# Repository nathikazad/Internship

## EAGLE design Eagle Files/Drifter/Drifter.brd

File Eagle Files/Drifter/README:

The PCB that got printed doest not have vcc connected on the RS485 chip, I updated that error on the eagle files afterwards

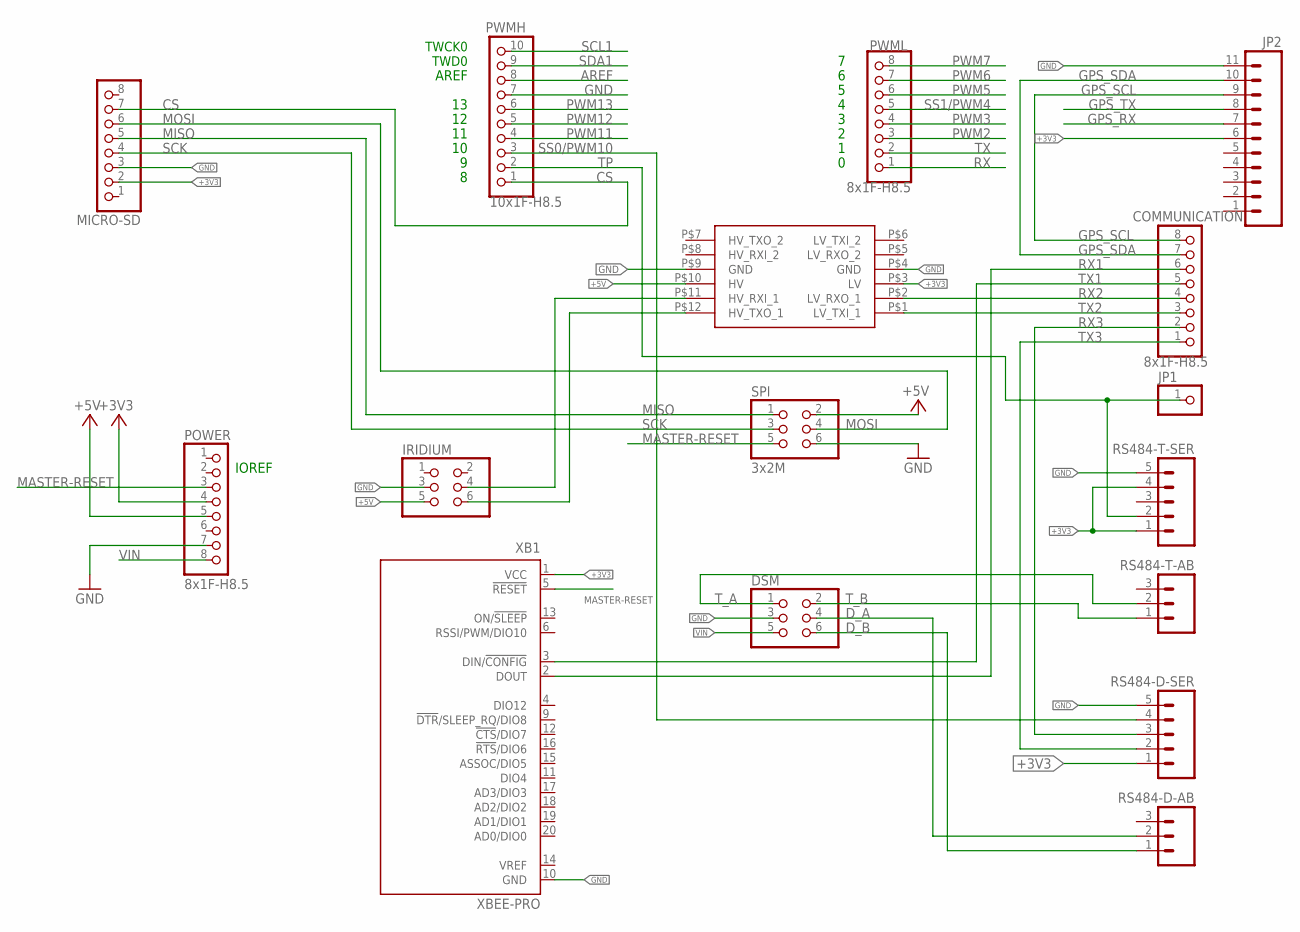
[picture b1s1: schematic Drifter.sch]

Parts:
COMMUNICATION: 8x1F-H8.5; 1X08
DSM: PINHD-2X3; 2X03
IRIDIUM: PINHD-2X3; 2X03
JP1: PINHD-1X1; 1X01
JP2: M111.27MM; 1X11-1.27MM
MICRO-SD: PINHD-1X8BIG; 1X08-BIG
POWER: 8x1F-H8.5; 1X08
PWMH: 10x1F-H8.5; 1X10
PWML: 8x1F-H8.5; 1X08
RS484-D-AB, RS484-T-AB: M03PTH; 1X03
RS484-D-SER, RS484-T-SER: M05PTH; 1X05
SPI: 3x2M; 2X03
U$1: LOGIC_LEVEL_CONVERTER
XB1: XBEE-PRO

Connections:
+3V3: JP2.6, MICRO-SD.2, POWER.4, RS484-D-SER.1, RS484-T-SER.1, RS484-T-SER.4, U$1.P$3 (LV), XB1.1 (VCC)
+5V: IRIDIUM.5, POWER.5, SPI.2, U$1.P$10 (HV)
AREF: PWMH.8
CS: MICRO-SD.7, PWMH.1
D_A: DSM.4, RS484-D-AB.2
D_B: DSM.6, RS484-D-AB.1
GND: DSM.3, IRIDIUM.3, JP2.11, MICRO-SD.3, POWER.7, PWMH.7, RS484-D-SER.5, RS484-T-SER.5, SPI.6, U$1.P$4 (GND), U$1.P$9 (GND), XB1.10 (GND)
GPS_RX: JP2.7
GPS_SCL: COMMUNICATION.8, JP2.9
GPS_SDA: COMMUNICATION.7, JP2.10
GPS_TX: JP2.8
MASTER-RESET: POWER.3, SPI.5, XB1.5 (!RESET)
MISO: MICRO-SD.5, SPI.1
MOSI: MICRO-SD.6, SPI.4
unnamed: IRIDIUM.4, U$1.P$11 (HV_RXI_1)
unnamed: IRIDIUM.6, U$1.P$12 (HV_TXO_1)
PWM2: PWML.3
PWM3: PWML.4
PWM5: PWML.6
PWM6: PWML.7
PWM7: PWML.8
PWM11: PWMH.4
PWM12: PWMH.5
PWM13: PWMH.6
RX: PWML.1
RX1: COMMUNICATION.6, XB1.2 (DOUT)
RX2: COMMUNICATION.4, U$1.P$2 (LV_RXO_1)
RX3: COMMUNICATION.2, RS484-D-SER.3
SCK: MICRO-SD.4, SPI.3
SCL1: PWMH.10
SDA1: PWMH.9
SS0/PWM10: PWMH.3, RS484-D-SER.4
SS1/PWM4: PWML.5
TP: JP1.1, PWMH.2, RS484-T-SER.2
TX: PWML.2
TX1: COMMUNICATION.5, XB1.3 (DIN/!CONFIG)
TX2: COMMUNICATION.3, U$1.P$1 (LV_TXI_1)
TX3: COMMUNICATION.1, RS484-D-SER.2
T_A: DSM.1, RS484-T-AB.2
T_B: DSM.2, RS484-T-AB.1
VIN: DSM.5, POWER.8

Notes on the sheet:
IOREF
TWCK0
TWD0
AREF

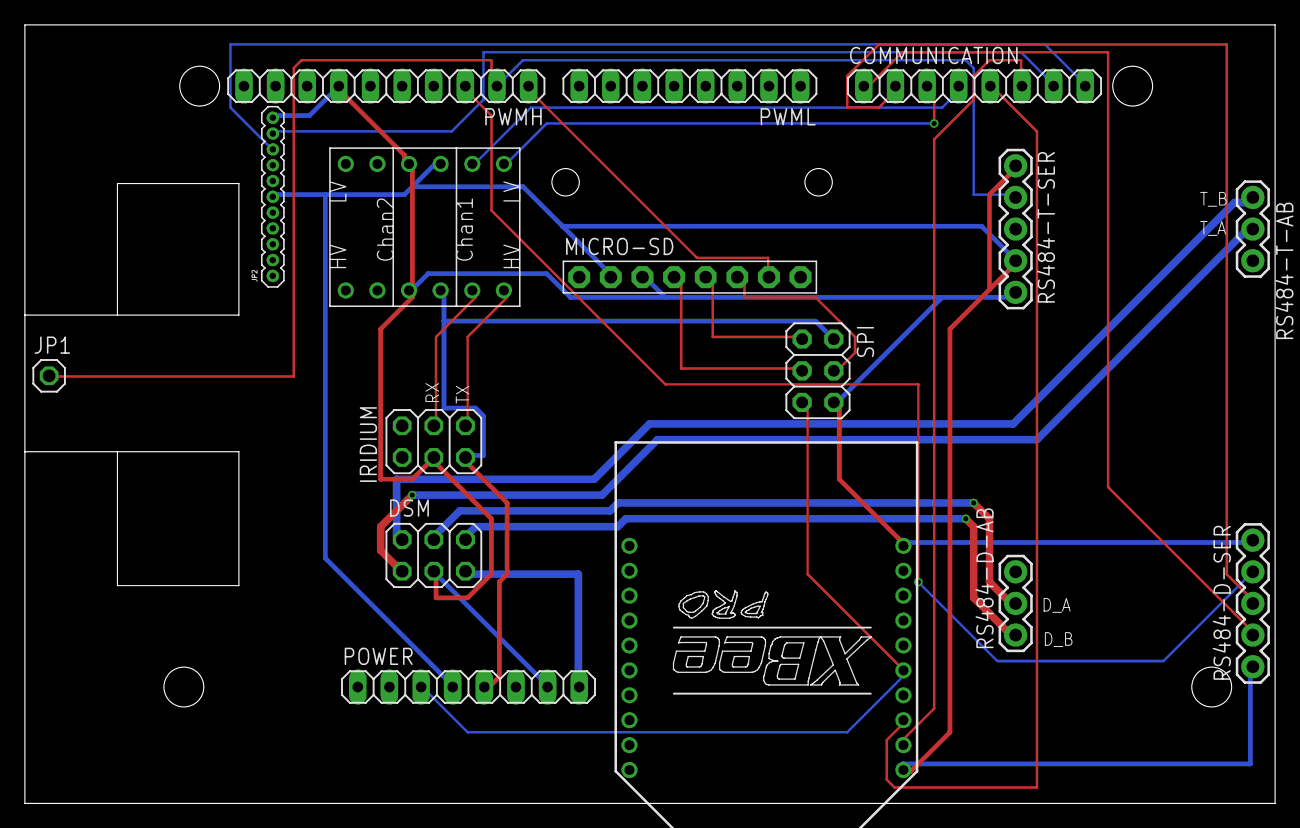
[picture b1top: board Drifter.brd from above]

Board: 2 copper layers, 100.4 x 62.5 mm, 16 parts (0 on the bottom side), 25 nets.

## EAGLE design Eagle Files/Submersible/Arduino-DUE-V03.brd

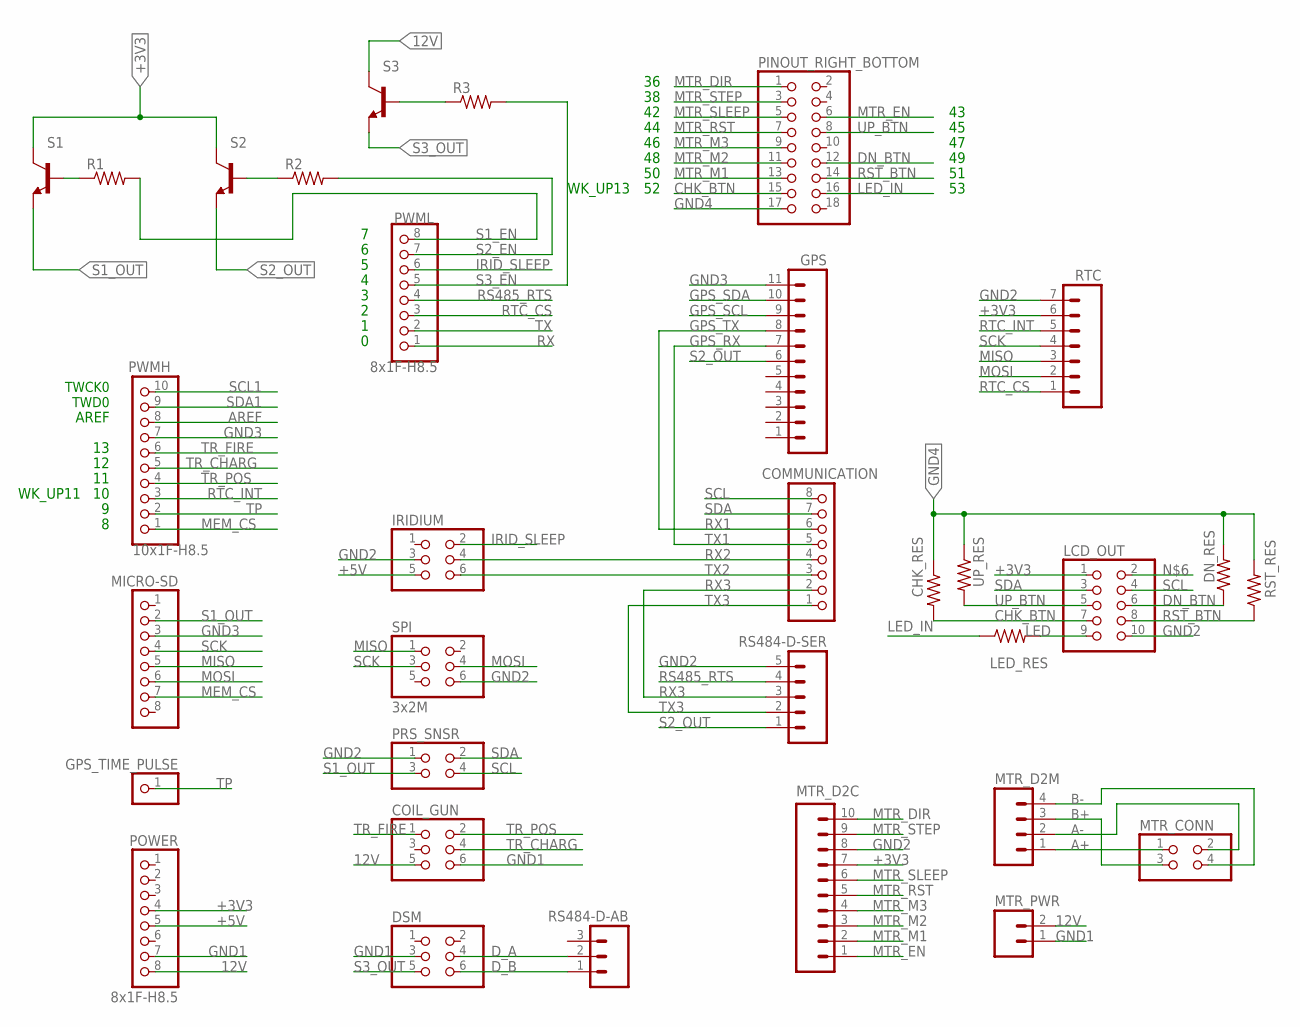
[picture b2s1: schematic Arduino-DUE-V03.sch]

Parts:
CHK_RES: RESISTORPTH-1/4W; AXIAL-0.4
COIL_GUN: PINHD-2X3; 2X03
COMMUNICATION: 8x1F-H8.5; 1X08
DN_RES: RESISTORPTH-1/4W; AXIAL-0.4
DSM: PINHD-2X3; 2X03
GPS: M111.27MM; 1X11-1.27MM
GPS_TIME_PULSE: PINHD-1X1; 1X01
IRIDIUM: PINHD-2X3; 2X03
LCD_OUT: PINHD-2X5; 2X05
LED_RES: RESISTORPTH-1/4W; AXIAL-0.4
MICRO-SD: PINHD-1X8BIG; 1X08-BIG
MTR_CONN: PINHD-2X2; 2X02
MTR_D2C: M10SILK_FEMALE_PTH; 1X10
MTR_D2M: M04NO_SILK_ALL_ROUND; 1X04_NO_SILK_ALL_ROUND
MTR_PWR: M02PTH; 1X02
PINOUT_RIGHT_BOTTOM: PINHD-2X9; 2X09
POWER: 8x1F-H8.5; 1X08
PRS_SNSR: PINHD-2X2; 2X02
PWMH: 10x1F-H8.5; 1X10
PWML: 8x1F-H8.5; 1X08
R1, R2, R3: RESISTORPTH-1/4W; AXIAL-0.4
RS484-D-AB: M03PTH; 1X03
RS484-D-SER: M05PTH; 1X05
RST_RES: RESISTORPTH-1/4W; AXIAL-0.4
RTC: M07; 1X07
S1, S2, S3: 2N3904; TO92
SPI: 3x2M; 2X03
UP_RES: RESISTORPTH-1/4W; AXIAL-0.4

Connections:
12V: COIL_GUN.5, MTR_PWR.2, POWER.8, S3.1 (C)
+3V3: LCD_OUT.1, MTR_D2C.7, POWER.4, RTC.6, S1.1 (C), S2.1 (C)
+5V: IRIDIUM.5, POWER.5
A+: MTR_CONN.1, MTR_D2M.1
A-: MTR_CONN.2, MTR_D2M.2
AREF: PWMH.8
B+: MTR_CONN.3, MTR_D2M.3
B-: MTR_CONN.4, MTR_D2M.4
CHK_BTN: CHK_RES.P$2 (2), LCD_OUT.7, PINOUT_RIGHT_BOTTOM.15
DN_BTN: DN_RES.P$1 (1), LCD_OUT.6, PINOUT_RIGHT_BOTTOM.12
D_A: DSM.4, RS484-D-AB.2
D_B: DSM.6, RS484-D-AB.1
GND1: COIL_GUN.6, DSM.3, MTR_PWR.1, POWER.7
GND2: IRIDIUM.3, LCD_OUT.10, MTR_D2C.8, PRS_SNSR.1, RS484-D-SER.5, RTC.7, SPI.6
GND3: GPS.11, MICRO-SD.3, PWMH.7
GND4: CHK_RES.P$1 (1), DN_RES.P$2 (2), PINOUT_RIGHT_BOTTOM.17, RST_RES.P$2 (2), UP_RES.P$1 (1)
GPS_RX: COMMUNICATION.5, GPS.7
GPS_SCL: GPS.9
GPS_SDA: GPS.10
GPS_TX: COMMUNICATION.6, GPS.8
IRID_SLEEP: IRIDIUM.2, PWML.6
LED: LCD_OUT.9, LED_RES.P$2 (2)
LED_IN: LED_RES.P$1 (1), PINOUT_RIGHT_BOTTOM.16
MEM_CS: MICRO-SD.7, PWMH.1
MISO: MICRO-SD.5, RTC.3, SPI.1
MOSI: MICRO-SD.6, RTC.2, SPI.4
MTR_DIR: MTR_D2C.10, PINOUT_RIGHT_BOTTOM.1
MTR_EN: MTR_D2C.1, PINOUT_RIGHT_BOTTOM.6
MTR_M1: MTR_D2C.2, PINOUT_RIGHT_BOTTOM.13
MTR_M2: MTR_D2C.3, PINOUT_RIGHT_BOTTOM.11
MTR_M3: MTR_D2C.4, PINOUT_RIGHT_BOTTOM.9
MTR_RST: MTR_D2C.5, PINOUT_RIGHT_BOTTOM.7
MTR_SLEEP: MTR_D2C.6, PINOUT_RIGHT_BOTTOM.5
MTR_STEP: MTR_D2C.9, PINOUT_RIGHT_BOTTOM.3
unnamed: R1.P$1 (1), S1.2 (B)
unnamed: R2.P$1 (1), S2.2 (B)
unnamed: R3.P$1 (1), S3.2 (B)
RS485_RTS: PWML.4, RS484-D-SER.4
RST_BTN: LCD_OUT.8, PINOUT_RIGHT_BOTTOM.14, RST_RES.P$1 (1)
RTC_CS: PWML.3, RTC.1
RTC_INT: PWMH.3, RTC.5
RX: PWML.1
RX2: COMMUNICATION.4, IRIDIUM.4
RX3: COMMUNICATION.2, RS484-D-SER.3
S1_EN: PWML.8, R1.P$2 (2)
S1_OUT: MICRO-SD.2, PRS_SNSR.3, S1.3 (E)
S2_EN: PWML.7, R2.P$2 (2)
S2_OUT: GPS.6, RS484-D-SER.1, S2.3 (E)
S3_EN: PWML.5, R3.P$2 (2)
S3_OUT: DSM.5, S3.3 (E)
SCK: MICRO-SD.4, RTC.4, SPI.3
SCL: COMMUNICATION.8, LCD_OUT.4, PRS_SNSR.4
SCL1: PWMH.10
SDA: COMMUNICATION.7, LCD_OUT.3, PRS_SNSR.2
SDA1: PWMH.9
TP: GPS_TIME_PULSE.1, PWMH.2
TR_CHARG: COIL_GUN.4, PWMH.5
TR_FIRE: COIL_GUN.1, PWMH.6
TR_POS: COIL_GUN.2, PWMH.4
TX: PWML.2
TX2: COMMUNICATION.3, IRIDIUM.6
TX3: COMMUNICATION.1, RS484-D-SER.2
UP_BTN: LCD_OUT.5, PINOUT_RIGHT_BOTTOM.8, UP_RES.P$2 (2)

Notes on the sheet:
TWCK0
TWD0
AREF
TX1
RX1
WK_UP11
WK_UP13

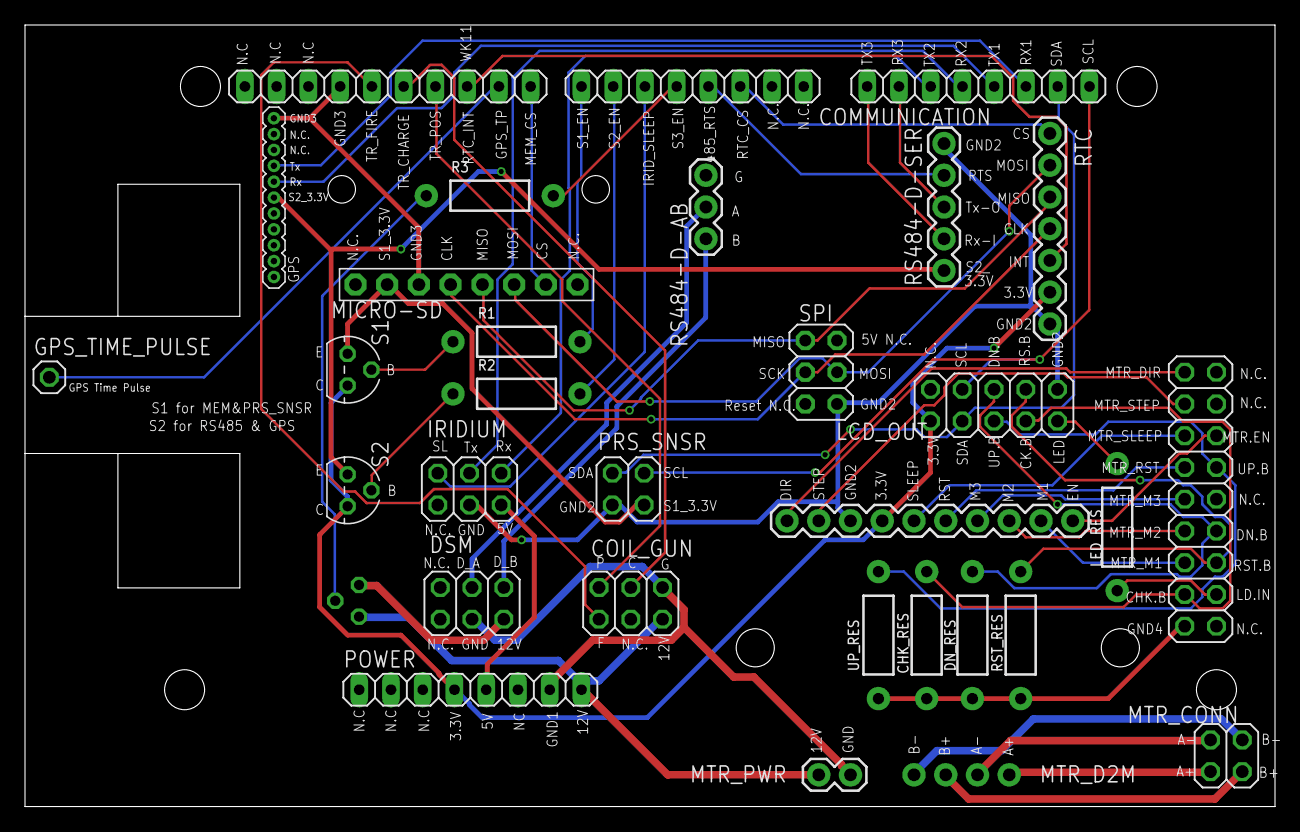
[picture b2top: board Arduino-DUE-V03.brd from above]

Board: 2 copper layers, 100.0 x 62.5 mm, 34 parts (1 on the bottom side), 56 nets.

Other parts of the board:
U$1, U$2: STAND-OFF-TIGHT

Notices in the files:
parts and their libraries:
SparkFun-Boards: Licensing: Creative Commons ShareAlike 4.0 International - https://creativecommons.org/licenses/by-sa/4.0
